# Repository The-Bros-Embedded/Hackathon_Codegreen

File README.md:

# Hackathon_Codegreen

These are the materials as Resyst provided for the Codegreen-Hackathon 2021 purpose.

#Resyst_team

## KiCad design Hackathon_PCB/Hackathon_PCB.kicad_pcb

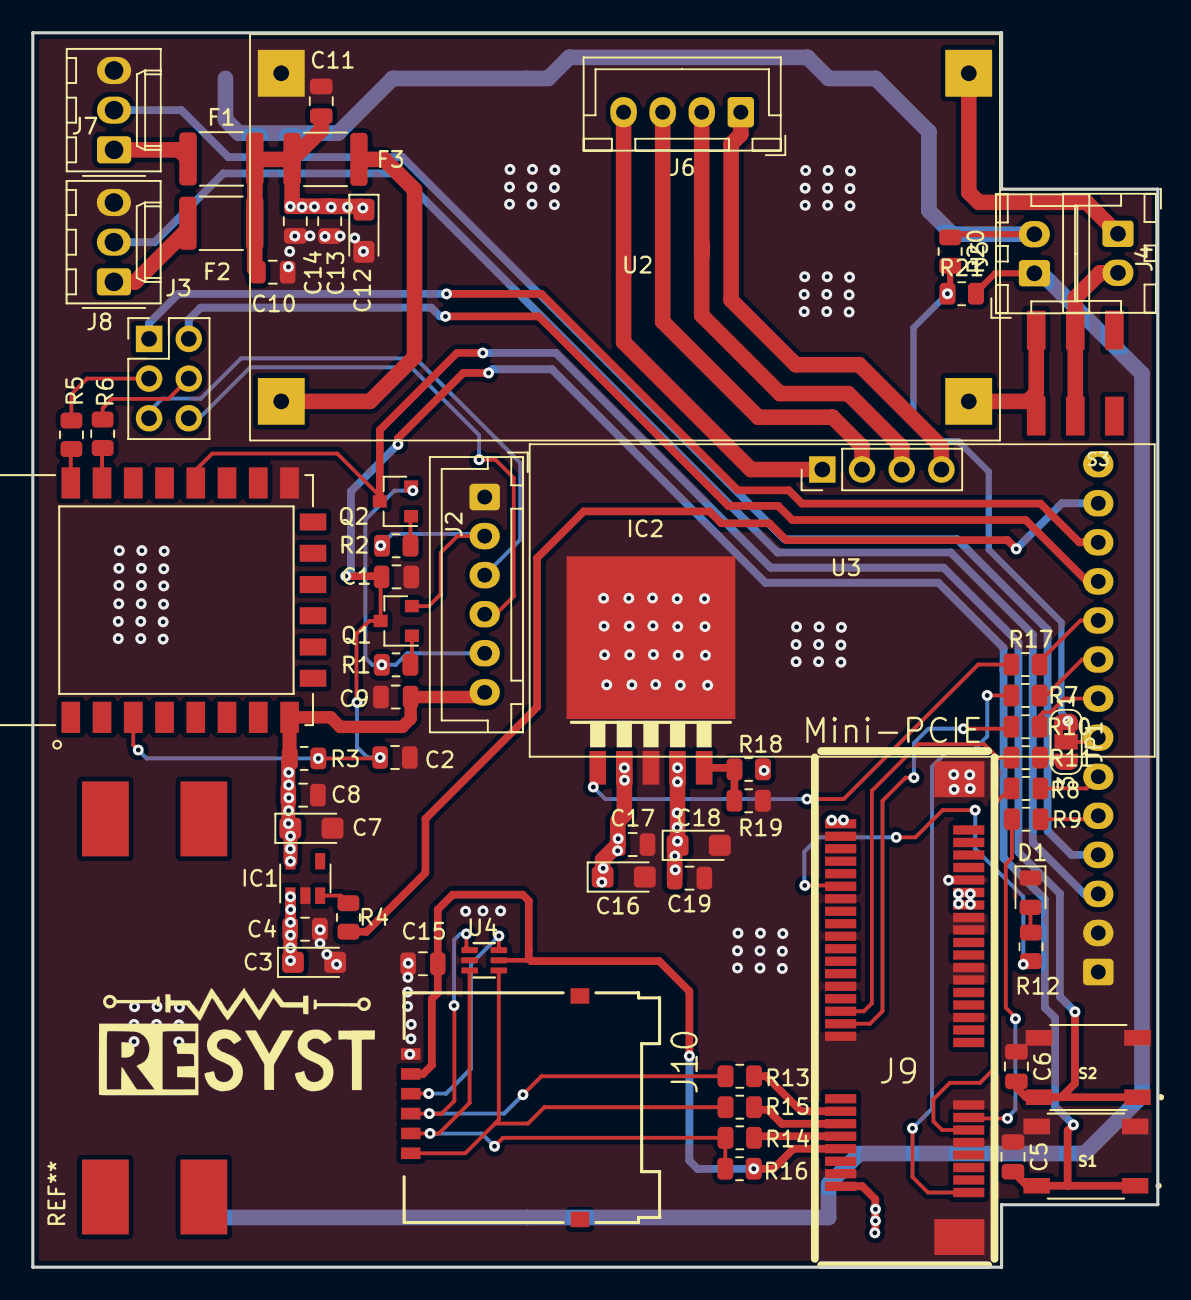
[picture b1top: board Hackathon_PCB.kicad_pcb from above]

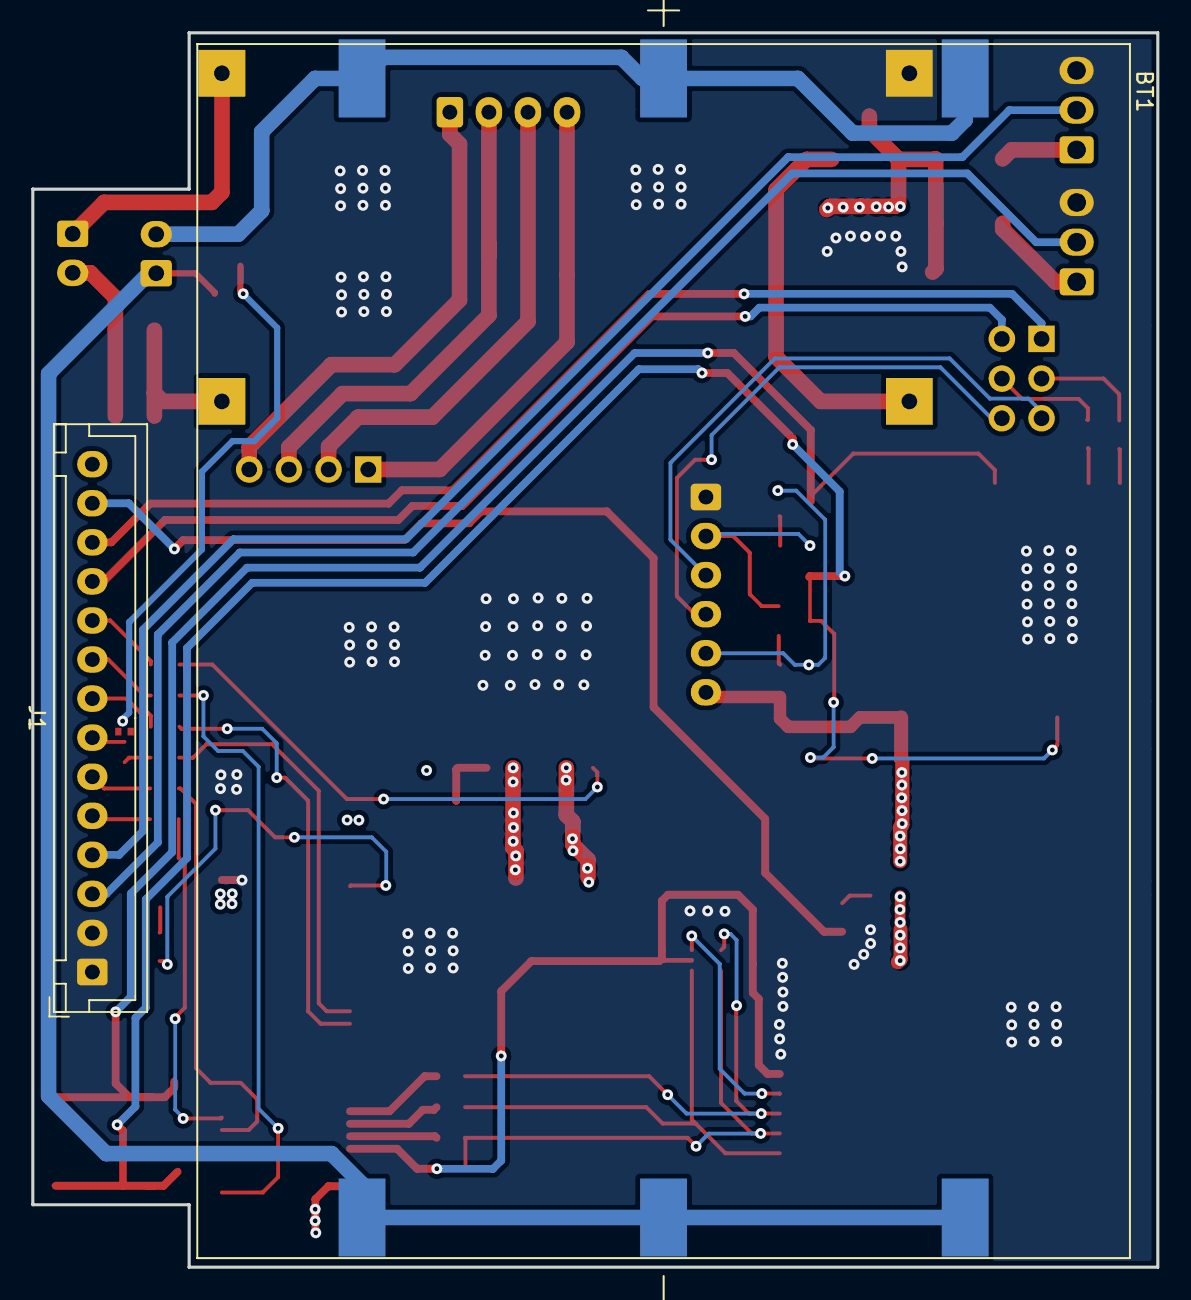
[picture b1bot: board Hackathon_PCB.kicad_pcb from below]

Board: 4 copper layers, 72.0 x 79.0 mm, 67 parts (2 on the bottom side), 59 nets.

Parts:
BT1: Holder-18650-3; BAT18650_Holder
C1, C2, C4, C5, C6, C8, C9, C10, C11, C14, C15: 100nf; C_0805_2012Metric
C3, C7: 1uF; CP_EIA-3216-18_Kemet-A
C12: 10uF; CP_EIA-3216-18_Kemet-A
C13: 1uF; C_0805_2012Metric
C16, C18: CP; CP_EIA-3216-18_Kemet-A
C17, C19: C; C_0805_2012Metric
D1: LED; LED_0805_2012Metric
F1, F2, F3: Polyfuse; Fuse_1812_4532Metric
IC1: ME6211; SOT-23-5
IC2: MIC29302WU
J1: Conn_01x14; JST_XH_B14B-XH-A_1x14_P2.50mm_Vertical
J2: Conn_01x06; JST_XH_B6B-XH-A_1x06_P2.50mm_Vertical
J3: Conn_02x03_Odd_Even; PinHeader_2x03_P2.54mm_Vertical
J4, J5: Conn_01x02; JST_XH_B2B-XH-A_1x02_P2.50mm_Vertical
J6: Conn_01x04; JST_XH_B4B-XH-A_1x04_P2.50mm_Vertical
J7, J8: Conn_01x03; Molex_KK-254_AE-6410-03A_1x03_P2.54mm_Vertical
J9: Mini-PCIE; mpcie-socket
J10: Simcard-Connector
JP1: Jumper_3_Bridged12; SolderJumper-3_P1.3mm_Bridged2Bar12_RoundedPad1.0x1.5mm_Num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
Q1, Q2: Q_NPN_BEC; SOT-23
R1, R2, R3: 10K; R_0805_2012Metric
R4: 1M; R_0805_2012Metric
R5, R6: 0; R_0805_2012Metric
R7, R8, R9, R10, R11, R12, R13, R14, R15, R17, R18, R19: 22; R_0805_2012Metric
R16: 15K; R_0805_2012Metric
R20, R21: R; R_0805_2012Metric
S1, S2: SW_Tactile
S3: SW_DPDT
U1: ESP32C3-12F; ESP8266
U2: Buck-boost-module
U3: solar_charger; Solar_Charger
U4: SMF05CT1G

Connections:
+5V: C3.1, C4.1, C10.1, C11.1, C12.1, C13.1, C14.1, C16.1, C17.1, F1.2, F2.2, F3.1, IC1.1, IC2.2, J1.14
/BAT_STAT: JP1.1, R20.2, R21.1
/DHT_DATA: J1.3, J8.2
/ESP32C3-12F-Minsys/CHIP_EN: C1.1, C2.1, C5.2, Q1.3, R3.1, S1.1, S1.2, U1.3
/ESP32C3-12F-Minsys/DTR: J2.5, Q2.2, R1.1
/ESP32C3-12F-Minsys/ESP_VCC: C7.1, C8.1, C9.2, IC1.5, J2.6, R3.2, U1.8
/ESP32C3-12F-Minsys/IO9: C6.2, Q2.3, S2.1, S2.2, U1.18
/ESP32C3-12F-Minsys/RTS: J2.2, Q1.2, R2.1
/ESP32C3-12F-Minsys/RXD: R6.2, U1.21
/ESP32C3-12F-Minsys/RXD0: J2.3, J3.5
/ESP32C3-12F-Minsys/TXD: R5.1, U1.22
/ESP32C3-12F-Minsys/TXD0: J2.4, J3.6
/ESP_EN: J1.13, R4.2
/ESP_RX: J1.12, J3.1
/ESP_TX: J1.11, J3.2
/GAS_DATA: J1.4, J7.2
/M_DIS: J1.8, R10.1
/M_EN: J1.10, R17.1
/M_PERST: JP1.3, R11.1
/M_RX: J1.6, R8.2
/M_TX: J1.5, R9.2
/M_WAKE: J1.9, R7.2
/Modem/SIM_CLK: J9.12, R15.2
/Modem/SIM_DATA: J9.10, R14.2
/Modem/SIM_RST: J9.14, R13.2
/Modem/SIM_VDD: C15.1, J9.8, J10.C1, R16.2, U4.5
/Modem/VCC_MODEM: C18.1, C19.1, IC2.4, J9.2, J9.39, J9.41, J9.52, R18.2
/PERST: J1.7, JP1.2
GND: C1.2, C2.2, C3.2, C4.2, C5.1, C6.1, C7.2, C8.2, C9.1, C10.2, C11.2, C12.2, C13.2, C14.2, C15.2, C16.2, C17.2, C18.2, C19.2, D1.1, IC1.2, IC2.3, IC2.6, J1.1, J1.2, J2.1, J7.3, J8.3, J9.4, J9.9, J9.15, J9.18, J9.21, J9.26, J9.27, J9.29, J9.34, J9.35, J9.37, J9.40, J9.43, J9.50, J9.SH1, J9.SH2, J10.C5, R19.1, S1.3, S1.4, S2.3, S2.4, U1.15, U2.3, U4.2
unnamed: BT1.1+, BT1.2+, BT1.3+, J5.2, R20.1
unnamed: BT1.1-, BT1.2-, BT1.3-, J5.1, R21.2
unnamed: D1.2, R12.1
unnamed: F1.1, J7.1
unnamed: F2.1, J8.1
unnamed: F3.2, U2.4
unnamed: IC1.3, R4.1
unnamed: IC2.1, R17.2
unnamed: IC2.5, R18.1, R19.2
unnamed: J3.3, R5.2
unnamed: J3.4, R6.1
unnamed: J4.1, U2.2
unnamed: J4.2, S3.2, S3.5
unnamed: J6.1, U3.4
unnamed: J6.2, U3.3
unnamed: J6.3, U3.2
unnamed: J6.4, U3.1
unnamed: J9.1, R7.1
unnamed: J9.11, R8.1
unnamed: J9.13, R9.1
unnamed: J9.20, R10.2
unnamed: J9.22, R11.2
unnamed: J9.42, R12.2
unnamed: J10.C2, R13.1, U4.1
unnamed: J10.C3, R15.1, U4.4
unnamed: J10.C6, U4.6
unnamed: J10.C7, R14.1, R16.1, U4.3
unnamed: Q1.1, R1.2
unnamed: Q2.1, R2.2
unnamed: S3.3, S3.6, U2.1

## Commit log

2021-11-15 initial commit
    initial commit
2021-11-21 commit
    commit
2021-11-23 initial commit
    commit
